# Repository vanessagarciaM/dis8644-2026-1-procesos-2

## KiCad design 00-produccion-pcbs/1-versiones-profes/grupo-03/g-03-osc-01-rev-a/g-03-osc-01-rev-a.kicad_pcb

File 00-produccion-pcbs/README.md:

# produccion-pcbs

jornada maratónica sábado 06 junio 2026

equipo docente toma todos los proyectos de kicad entregados el día anterior, de proyecto-02, y con eso edita, revisa, y envía a producción.

hay 6 grupos de trabajo con una temática en particular, cada grupo realizó 2 esquemáticos con sus respectivas placas, en varias versiones que subieron a la carpeta 00-proyecto-02.

a continuación los apuntes de las distintas revisiones hechas de estos proyectos, para prepararlos para su producción física.

en este repo creamos 3 carpetas:

- 0-versiones-estudiantes: archivos de kicad con las versiones más recientes de proyectos de estudiantes
- 1-versiones-profes: archivos de kicad con las versiones revisadas y realizadas por equipo docentes
- 2-archivos-produccion: gerbers de producción, etiquetados como revA.

## grupo-01: piezos

- benjaminalvarez21
- Anaysval
- chknngttts
- ryukivol
- nicolasvaldesgreve

### g-01-pie-01-rev-a

- cambiamos tamaño r15
- cambiamos conector de entrada
- cambiamos nomenclatura de "100 u" a "100u"
- cambiamos huella de transistor Q1, porque era la equivocada

### g-01-pie-02-rev-a

- no fue enviado a producción porque no tenemos garantía de que funcionara según lo visto en protoboard.

## grupo-02: secuenciadores

- isidoraalvarez
- tomascatri
- dayanapanitrur
- Estrabismx
- angel-udp

### g-02-sec-01-rev-a

en esquemático:

- agregamos resistor de clock in a ground, para pulldown.
- agregamos resistor entre 4040 Q0 patita 9 y salida
- agregamos resistor a cada salida de jack switch.
- cambiamos huellas de transistores a versión inline_wide para que tengan más espacio
- agregados mounting hole faltantes

en pcb:

- actualizamos conectores jack a la huella de la biblioteca, para poder rutear bien los nuevos resistores y no perdernos.

### g-02-sec-02-rev-a

en esquemático:

- agregamos también resistores de protección en entradas y salidas.
- agregados mounting hole faltantes

en pcb:

- actualizamos conectores jack a la huella de la biblioteca, para poder rutear bien los nuevos resistores y no perdernos.

## grupo-03: osciladores 1

- vanessagarciaM
- antoloch
- ccarlabelenn
- arielorozco024
- Narelyriquelme

## grupo-04: osciladores 2

- antokiaraa
- santiagocifuvelez
- paulafuentesm
- kristelagj
- catalinaoyanedel
- yairaruiz

## grupo-05: filtros

- antoniaamc
- Catabalboa
- sebastianguevaralarotta
- CatalinaJeria
- Luisaatoro9

### g-05-fil-01-rev-a

- error grave en la nomenclatura de los proyectos: el 01 en su README dicen que es el activo, pero en Kicad es el pasivo
- cambiamos C1 por condensador no polarizado
- conectamos patita del medio de potenciómetro
- confusión en los tamaños de los condensadores C4 y C5

### g-05-fil-02-rev-a

- - error grave en la nomenclatura de los proyectos: el 01 en su README dicen que es el activo, pero en Kicad es el pasivo

## grupo-06: percusiones

- terroiblea
- martinaechavarria-stack
- Nicolas-Miranda1312
- paredesvania
- Coff4

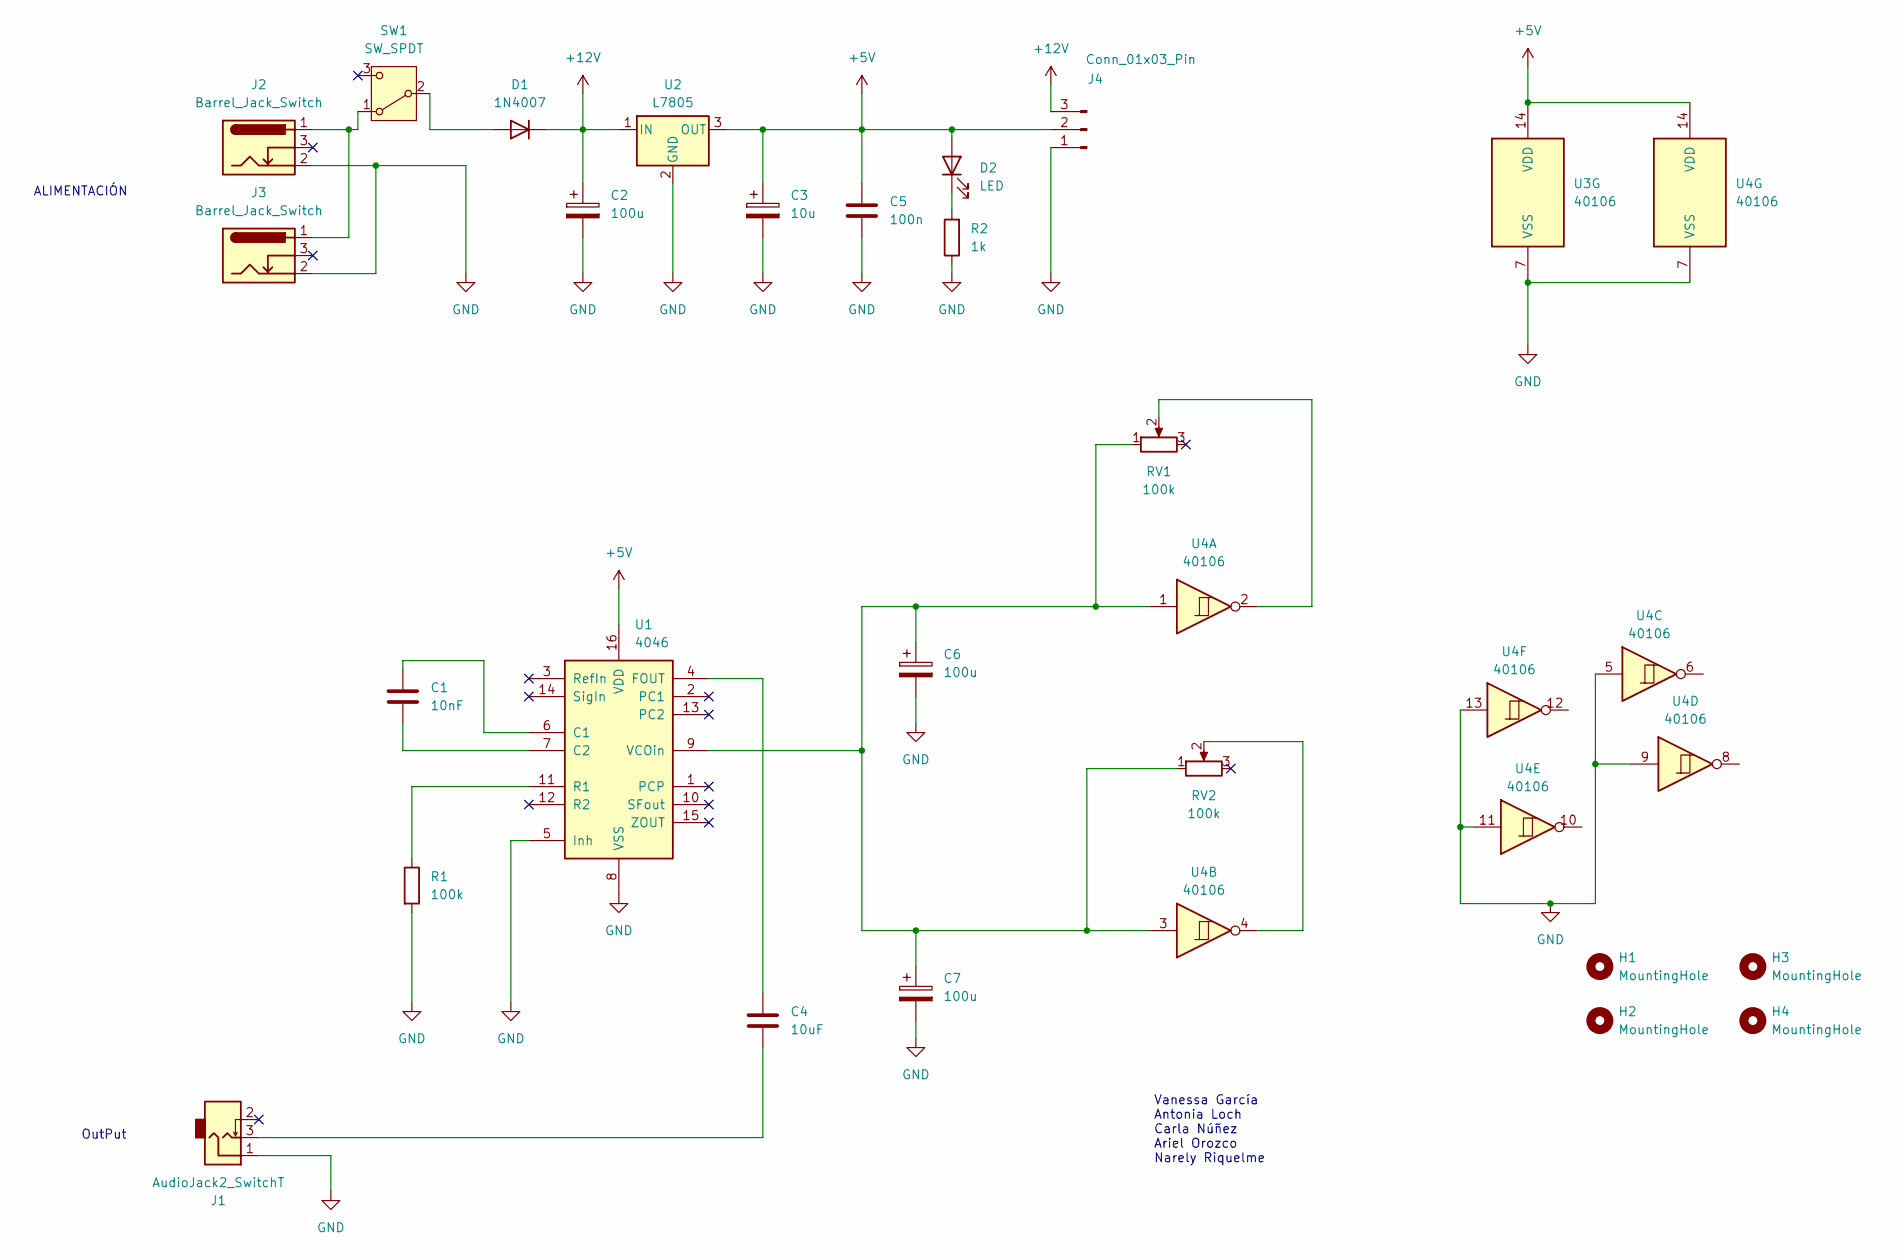
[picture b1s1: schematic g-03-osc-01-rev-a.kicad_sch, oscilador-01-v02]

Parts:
C1: 10nF; C_Disc_D3.8mm_W2.6mm_P2.50mm
C2, C6, C7: 100u; CP_Radial_D8.0mm_P3.80mm
C3: 10u; CP_Radial_D4.0mm_P2.00mm
C4: 10uF; CP_Radial_D5.0mm_P2.00mm
C5: 100n; C_Disc_D5.0mm_W2.5mm_P2.50mm
D1: 1N4007; D_DO-41_SOD81_P10.16mm_Horizontal
D2: LED; LED_D5.0mm
H1, H2, H3, H4: MountingHole; MountingHole_3.2mm_M3
J1: AudioJack2_SwitchT; PJ301M-12
J2, J3: Barrel_Jack_Switch; BarrelJack_Horizontal
J4: Conn_01x03_Pin; PinSocket_1x03_P2.54mm_Vertical
R1: 100k; R_Axial_DIN0207_L6.3mm_D2.5mm_P10.16mm_Horizontal
R2: 1k; R_Axial_DIN0207_L6.3mm_D2.5mm_P10.16mm_Horizontal
RV1, RV2: 100k; Potentiometer_Alps_RK163_Single_Horizontal
SW1: SW_SPDT; spdt_ssd12d00g3
U1: 4046; DIP-16_W7.62mm_LongPads
U2: L7805; TO-220-3_Horizontal_TabDown
U3: 40106; DIP-14_W7.62mm_LongPads
U4: 40106

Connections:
+5V: C3.1, C5.1, D2.2 (A), J4.2, U1.16 (VDD), U2.3 (OUT), U3.14 (VDD), U4.14 (VDD)
+12V: C2.1, D1.1 (K), J4.3, U2.1 (IN)
GND: C2.2, C3.2, C5.2, C6.2, C7.2, J1.1, J2.2, J3.2, J4.1, R1.2, R2.1, U1.5 (Inh), U1.8 (VSS), U2.2 (GND), U3.7 (VSS), U4.5, U4.7 (VSS), U4.9, U4.11, U4.13
unnamed: C4.2, J1.3
unnamed: D1.2 (A), SW1.2 (B)
unnamed: D2.1 (K), R2.2
unnamed: RV1.2, U4.2
unnamed: RV2.2, U4.4
unnamed: J2.1, J3.1, SW1.1 (A)
unnamed: C1.2, U1.6 (C1)
unnamed: C1.1, U1.7 (C2)
unnamed: C4.1, U1.4 (FOUT)
unnamed: R1.1, U1.11 (R1)
unnamed: C6.1, C7.1, RV1.1, RV2.1, U1.9 (VCOin), U4.1, U4.3

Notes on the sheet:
ALIMENTACIÓN
OutPut
Vanessa García Antonia Loch Carla Núñez Ariel Orozco Narely Riquelme

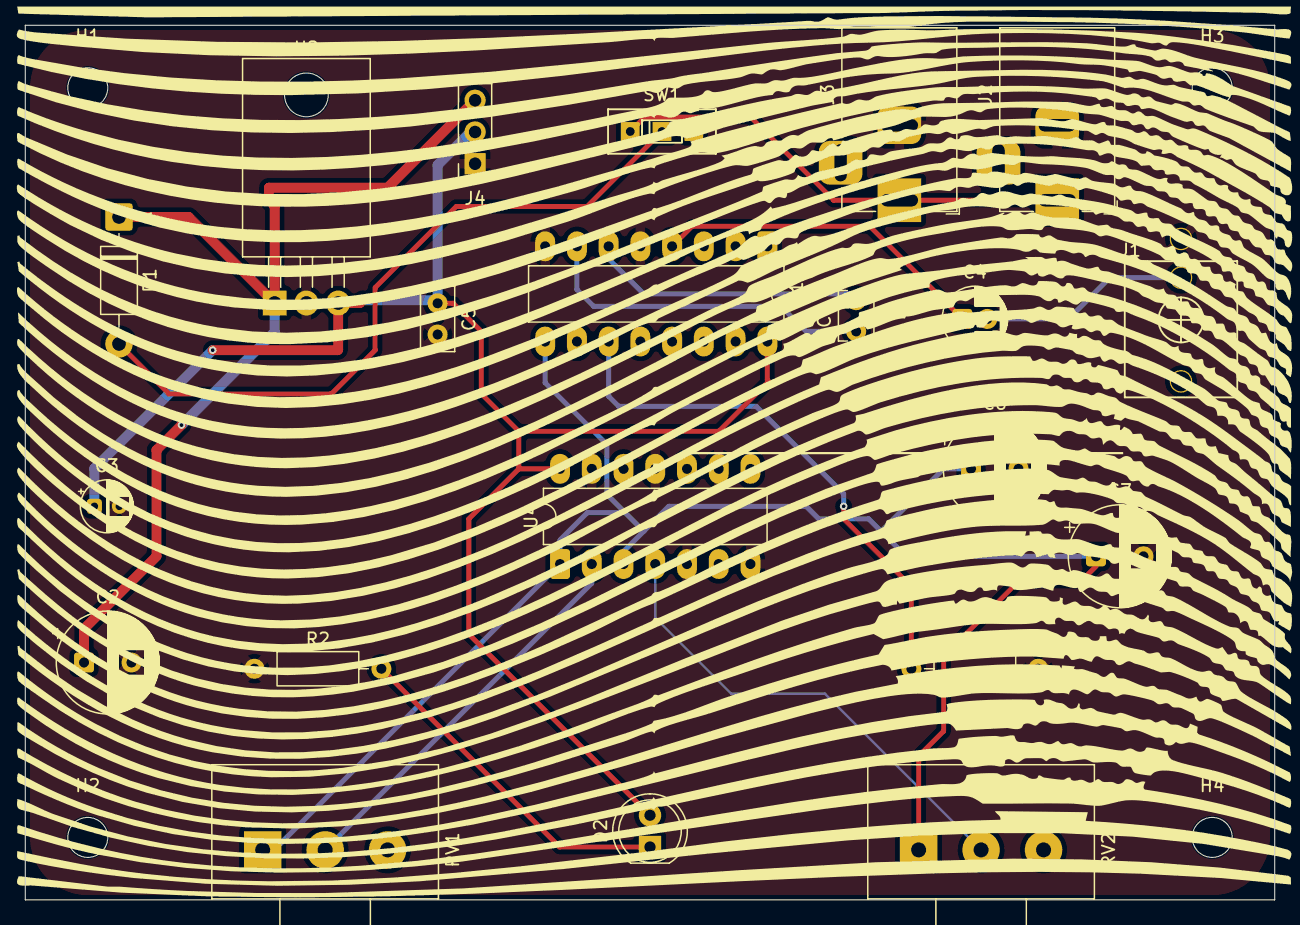
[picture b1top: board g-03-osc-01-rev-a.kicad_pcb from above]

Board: 2 copper layers, 100.0 x 70.0 mm, 25 parts (0 on the bottom side), 14 nets.

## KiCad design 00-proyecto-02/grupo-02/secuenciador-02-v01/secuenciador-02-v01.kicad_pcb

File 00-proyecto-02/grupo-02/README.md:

# proyecto-02

## Grupo

Número de grupo: 02

Tema del grupo: Secuenciador 

Integrantes:

- Isidora Alvarez / isidoraalvarez
- Dayana Pañitrur / dayanapanitrur
- Camila Ramirez / Estrabismx
- Angel Sabogal / angel-udp
- Tomas Catrileo / tomascatri
  
## Circuito 1 v01: Contador binario - CD4040

### Descripción general/conceptual 1

¿Qué hace el circuito? Intentar explicarlo para gente que no sabe electrónica. Ejemplo: escucha los impactos sobre sí mismo y lo convierte en señales de aviso para otras cosas

Este circuito se categoriza como un secuenciador, es decir que genera corrientes eléctricas en un patrón repetitivo y ordenado. Un ejemplo de esto es un semáforo, ya que se va a prender siempre en el mismo orden:

_VERDE > AMARILLO > ROJO > VERDE > AMARILLO > ROJO > ..._

<br>

### Descripción de funcionamiento 1

Preguntas orientadoras: ¿Qué inputs recibe? ¿Qué outputs entrega? ¿Cómo administra los flujos de inputs a outputs internamente? ¿Qué componente es el "corazón/cerebro"? ¿Qué truco descubrimos en el camino? ¿Especulativamente, qué se podría conectar a este módulo en el futuro?

<br>

Ya definimos que este sistema es un secuenciador, pero algo importante es como está configurada la duración de cada _activación_. Tal como en los semáforos no todos los colores duran lo mismo, en este circuito cada _señal_ tiene una duración única. ¿A que se refiere "duración unica"? En que cada _señal_ está asociada a un número, desde el 0 al 12 y mientras menor sea el número asociado, más rapido se va a _activar_. A continuación se puede observar una representación de este patrón

> De izquierda a derecha: Avance del tiempo
>
> De arriba a abajo: Q1, Q2, Q3, Q4 y Q5 = Canales

<br>

Esta es una secuencia binaria y de las cosas más notorias es que cada _canal_ tiene la misma duración prendido y apagado, es decir, el Q3 funciona con 4 _señales apagadas_ y 4 _señales prendidas_. Otro punto interesante es como esta duración tambien sigue un patrón

| Canal / Step | Duración   |
| ------------ | ---------- |
| Q1           | 1 tiempo   |
| Q2           | 2 tiempos  |
| Q3           | 4 tiempos  |
| Q4           | 8 tiempos  |
| Q5           | 16 tiempos |

<br>

Ahora que entendemos como funciona su secuencia, vamos a profundizar más en como este circuito logra generar este proceso. Anteriormente se mencionó (y tmabien se ejemplificó en la imagen) que en cada _"tiempo"_ se van _activando_ las señales correspondientes, estos "_tiempos_" son corrientes eléctricas, es decir, que se necesita una señal intermitente y constante para activar el proceso de conteo. Esto es conocido como **reloj** o **clock**, entonces la velocidad con la que alterne este circuito afectará en como nuestro secuenciador realice su conteo.

Para una mayor compresión se utilizará la siguiente analogía: Tenemos una especie de corazón (Reloj) que cada vez que late (emitir un pulso eléctrico) un semáforo prende sus luces (se activan las salidas del secuenciador)

>Clickear imagen para reproducir video

### Esquemático 

### PCB 1

### Documentación audiovisual funcionamiento protoboard 1

Clickear imagenes para reproducir video

<br>

## Circuito 2

Circuito 2 v01:  registro de desplazamiento estático - CD4015

### Descripción general/conceptual 2

¿Qué hace el circuito? Intentar explicarlo para gente que no sabe electrónica. Ejemplo: escucha los impactos sobre sí mismo y lo convierte en señales de aviso para otras cosas

Este circuito también se categoriza como un secuenciador, es decir, que genera corrientes eléctricas en un patrón repetitivo y ordenado. Podemos tomar el mismo ejemplo del semáforo mencionado en el circuito anterior, donde este funciona encendiendo un LED detrás del otro sucesivamente hasta que se repite el ciclo.

### Descripción de funcionamiento 2

Preguntas orientadoras: ¿Qué inputs recibe? ¿Qué outputs entrega? ¿Cómo administra los flujos de inputs a outputs internamente? ¿Qué componente es el "corazón/cerebro"? ¿Qué truco descubrimos en el camino? ¿Especulativamente, qué se podría conectar a este módulo en el futuro?

¿Qué inputs recibe?
Recibe una señal de reloj (clock), que son pulsos eléctricos que le indican cuándo debe avanzar al siguiente paso de la secuencia puede venir de un chip NE555.

¿Qué outputs entrega?
Entrega señales eléctricas en sus distintas salidas (Q1, Q2, Q3, ..., Q8), activando una salida tras otra en orden.

¿Cómo administra los flujos de inputs a outputs internamente?
Cada vez que llega un pulso del reloj "del chip 555", el CD4015 mueve la información al siguiente paso.

¿Qué componente es el corazón o cerebro?
El componente principal es el chip CD4015, ya que es el encargado de guardar y mover la información entre sus salidas siguiendo el ritmo del reloj.

¿Qué truco descubrimos en el camino?
Se cambio la resistencia del 555 de 1k a 15k y logramos hacer el circuito mas estable.

¿Qué se podría conectar a este módulo en el futuro?
Se podrían conectar LEDs, sintetizadores, relés, motores o cualquier circuito que necesite activarse siguiendo una secuencia automática.

### Esquemático 2

### PCB 2

```markdown

```

```markdown

```

### Documentación audiovisual funcionamiento protoboard 2

Incluir enlace a video en youtube (puede estar en Oculto) con protoboard funcionando

## Otros circuitos

¿Usaron otro circuito temporal para activar algunas cosas? ¿para probar inputs-outputs? Detallar cuales

## Colaboración con otros grupos

### ¿Cómo ayudé a otro grupo?

Lorem ipsum

### ¿Cómo me ayudó otro grupo?

lorem ipsum

## Bibliografía

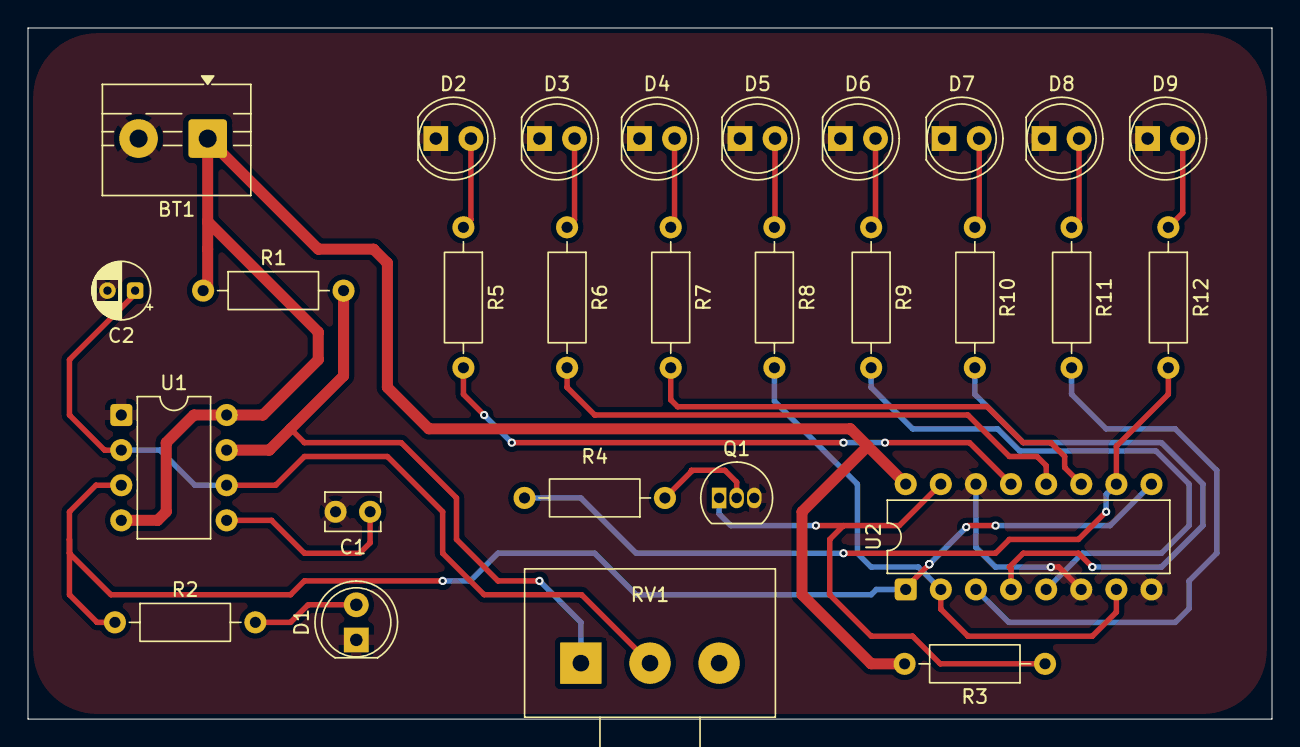
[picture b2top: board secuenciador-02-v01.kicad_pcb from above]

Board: 2 copper layers, 90.0 x 50.0 mm, 28 parts (0 on the bottom side), 25 nets.

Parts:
BT1: 9V; TerminalBlock_MaiXu_MX126-5.0-02P_1x02_P5.00mm
C1: 100n; C_Disc_D3.8mm_W2.6mm_P2.50mm
C2: 1uF; CP_Radial_D4.0mm_P2.00mm
D1, D2, D3, D4, D5, D6, D7, D8, D9: LED; LED_D5.0mm
Q1: BC548; TO-92_Inline
R1, R2: 15k; R_Axial_DIN0207_L6.3mm_D2.5mm_P10.16mm_Horizontal
R3: 1k; R_Axial_DIN0207_L6.3mm_D2.5mm_P10.16mm_Horizontal
R4: 10k; R_Axial_DIN0207_L6.3mm_D2.5mm_P10.16mm_Horizontal
R5, R6, R7, R8, R9, R10, R11, R12: 220; R_Axial_DIN0207_L6.3mm_D2.5mm_P10.16mm_Horizontal
RV1: 100k; Potentiometer_Alps_RK163_Single_Horizontal
U1: NE555P; DIP-8_W7.62mm
U2: 4015; DIP-16_W7.62mm

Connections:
GND: BT1.2 (-), C1.2, C2.2, D1.1 (K), D2.1 (K), D3.1 (K), D4.1 (K), D5.1 (K), D6.1 (K), D7.1 (K), D8.1 (K), D9.1 (K), Q1.3 (E), U1.1 (GND), U2.6 (MR), U2.8 (Vss), U2.14 (MR)
unnamed: D1.2 (A), R2.2
unnamed: D2.2 (A), R5.1
unnamed: D3.2 (A), R6.1
unnamed: D4.2 (A), R7.1
unnamed: D5.2 (A), R8.1
unnamed: D6.2 (A), R9.1
unnamed: D7.2 (A), R10.1
unnamed: D8.2 (A), R11.1
unnamed: D9.2 (A), R12.1
unnamed: Q1.2 (B), R4.1
unnamed: Q1.1 (C), R3.1, U2.15 (D)
unnamed: C1.1, U1.5 (CONT)
unnamed: R1.2, RV1.1, U1.7 (DIS)
unnamed: R2.1, U1.3 (OUT), U2.1 (CP), U2.9 (CP)
unnamed: C2.1, RV1.2, U1.2 (TRIG), U1.6 (THR)
unnamed: R8.2, U2.2 (Q4), U2.7 (D)
unnamed: R9.2, U2.5 (Q1)
unnamed: R10.2, U2.4 (Q2)
unnamed: R11.2, U2.3 (Q3)
unnamed: R4.2, R12.2, U2.10 (Q4)
unnamed: R5.2, U2.13 (Q1)
unnamed: R6.2, U2.12 (Q2)
unnamed: R7.2, U2.11 (Q3)
VCC: BT1.1 (+), R1.1, R3.2, U1.4 (~RST), U1.8 (VCC), U2.16 (Vdd)

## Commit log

2026-05-15 Rename Captura de pantalla 2026-05-14 220701.png to proceso
2026-05-15 Rename imagen6.PNG to imagen6.png
2026-05-15 apuntes clase
2026-05-15 Update README with additional content and corrections
2026-05-18 Update README.md with session 10a details
    Added detailed instructions for session 10a, including project requirements and reading assignments.
2026-05-19 error-tamano
2026-05-19 Add notes about chapters 2 and 3 to README
2026-05-20 agregar
2026-05-21 Fix image reference in README.md
2026-05-22 agrego apuntes
2026-05-22 agregar instrucciones
2026-05-22 agregar carpeta imagenes
2026-05-22 sesion-in-correcta
2026-05-24 agrego apuntes libro
2026-05-25 Receso academico.md
2026-05-25 Agregar imagen
2026-05-26 crear carpeta!!
2026-05-26 Update README with session details and materials
    Added details about class introduction, materials used, and advice for unused pins.
2026-05-26 Rename esquematico-1.png.png to esquematico-1.png
2026-05-27 añadir-texto-flusser-4-5
2026-05-29 Rename Captura de pantalla 2026-05-29 100950.png to circuito-cd4015.png
2026-05-31 arreglo redacción
2026-06-02 avance-apunte-falta-mover-imagenes
2026-06-02 Revise README for session 11a updates
    Updated session details from session 10a to session 11a, including new content and structure.
2026-06-03 cambiar-carpeta
2026-06-04 agrego esquematico 2
2026-06-05 eliminar archivo borrar
2026-06-05 Rename comunicacion.jpg.jpg to comunicacion.jpg
2026-06-05 pcb arreglada clase 05/06
2026-06-06 agregar apuntes
2026-06-06 agregar mas apuntes sobre grupo-01
2026-06-06 agregar mas apuntes
2026-06-06 añadido g03-01
2026-06-09 Update README with PCB export instructions and references
    Added detailed instructions on exporting PCB files and information about guitar pedals and references.
2026-06-12 Update README.md with chapter assignment details
2026-06-14 Refine text in README.md for clarity and flow
2026-06-14 Fix header formatting in README.md
2026-06-15 Update README with project organization and filter info
    Added project organization details and filter explanations.
2026-06-17 agrego libro
